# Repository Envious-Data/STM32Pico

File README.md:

# STM32Pico
A STM32 board in the format of a raspberry pi pico.

Im making this just so I can test out some other MCUs and also learn more about MCU board design, because I have things that use the raspberry pi pico I would like to make some replacements if there is a particular use case.

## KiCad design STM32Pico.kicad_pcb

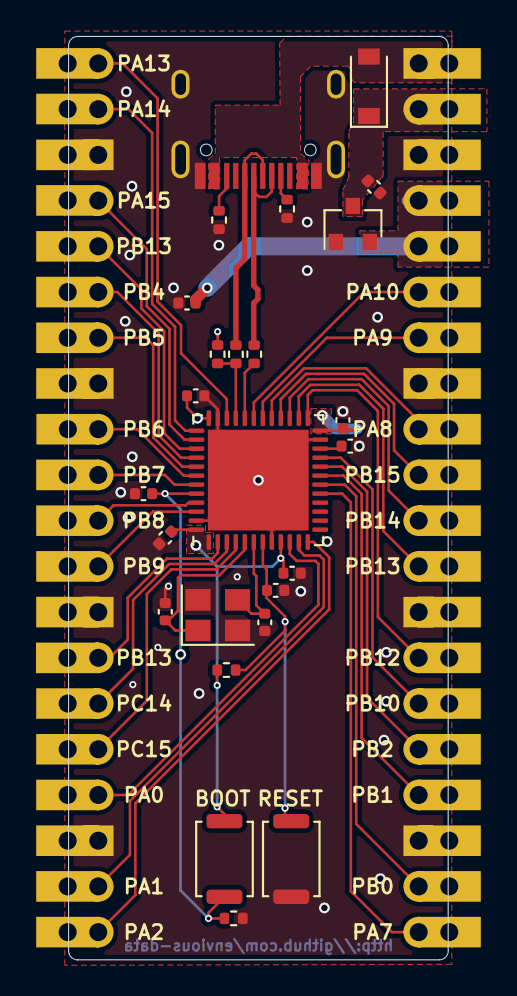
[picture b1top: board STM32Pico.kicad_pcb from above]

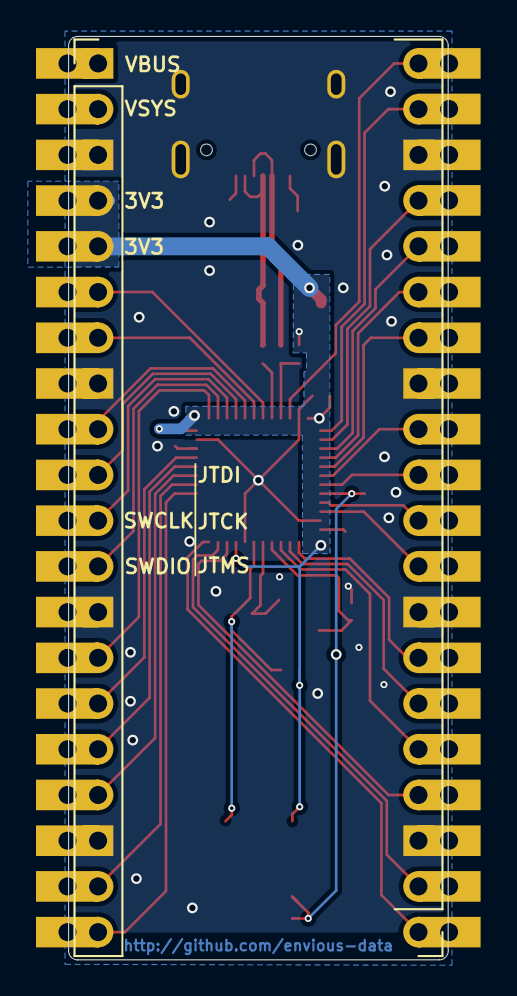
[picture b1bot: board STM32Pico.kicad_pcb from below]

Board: 2 copper layers, 21.1 x 51.3 mm, 27 parts (2 on the bottom side), 43 nets.

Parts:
C1: 2.2uF 0402; C_0402_1005Metric
C2, C3, C4, C5: 100nf capacitor; C_0402_1005Metric
C6, C7: 1uf capacitor; C_0402_1005Metric
C8, C9: 100nf 0402; C_0402_1005Metric
C10, C11: 22pf capacitor; C_0402_1005Metric
D1: 1N4002; D_SOD-123
J1, J2: 2.54mm header 01x20; PinHeader_1x20_P2.54mm_Vertical
R1, R2: 5.1K 0402; R_0402_1005Metric
R3, R4: 22ohm; R_0402_1005Metric
R5: 1.5K 0402; R_0402_1005Metric
R6: 10K 0402; R_0402_1005Metric
R7: 100k 0402; R_0402_1005Metric
SW1: Boot Mode; SW_Push_SPST_NO_Alps_SKRK
SW2: Reset Switch; SW_Push_SPST_NO_Alps_SKRK
U1: STM32F411CEUx; QFN-48-1EP_7x7mm_P0.5mm_EP5.6x5.6mm
U2: XC6206PxxxMR; SOT-23
USB1: HRO-TYPE-C-31-M-12; HRO-TYPE-C-31-M-12-Assembly
Y1: 8Mhz 3225; Crystal_SMD_3225-4Pin_3.2x2.5mm

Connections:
+3V3: C2.1, C3.2, C4.2, C5.2, C7.2, J2.4, J2.5, R5.1, R6.2, SW1.1, U1.1, U1.9, U1.24, U1.36, U1.48, U2.2
D+: R3.2, USB1.6, USB1.8
D-: R4.2, USB1.5, USB1.7
GND: C1.1, C2.2, C3.1, C4.1, C5.1, C6.1, C7.1, C8.2, C9.2, C10.2, C11.2, J1.3, J1.8, J1.13, J1.18, J2.3, J2.8, J2.13, J2.18, R1.1, R2.1, R7.2, SW2.1, U1.8, U1.23, U1.35, U1.47, U1.49, U2.1, USB1.1, USB1.12, USB1.13, Y1.2, Y1.4
unnamed: C1.2, U1.22
unnamed: R1.2, USB1.4
unnamed: R2.2, USB1.10
OSCIN: C10.1, U1.5, Y1.1
OSCOUT: C11.1, U1.6, Y1.3
PA0: J1.4, U1.10
PA1: J1.2, U1.11
PA2: J1.1, U1.12
PA7: J2.20, U1.17
PA8: J2.9, U1.29
PA9: J2.7, U1.30
PA10: J2.6, U1.31
PA11: R4.1, U1.32
PA12: R3.1, R5.2, U1.33
PA13-SWDIO: J1.20, U1.34
PA14-SWCLK: J1.19, U1.37
PA15: J1.17, U1.38
PB0: J2.19, U1.18
PB1: J2.17, U1.19
PB2: J2.16, U1.20
PB3: J1.16, U1.39
PB4: J1.15, U1.40
PB5: J1.14, U1.41
PB6: J1.12, U1.42
PB7: J1.11, U1.43
PB8: J1.10, U1.45
PB9: J1.9, U1.46
PB10: J2.15, U1.21
PB12: J2.14, U1.25
PB13: J2.12, U1.26
PB14: J2.11, U1.27
PB15: J2.10, U1.28
PC13: J1.7, U1.2
PC14: J1.6, U1.3
PC15: J1.5, U1.4
VBUS: D1.2, J2.1, USB1.2, USB1.11
VSYS: C6.2, D1.1, J2.2, U2.3
boot0: C8.1, R7.1, SW1.2, U1.44
resetsw: C9.1, R6.1, SW2.2, U1.7

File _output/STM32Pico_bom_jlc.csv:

"Comment","Designator","Footprint","LCSC Part #"
"2.2uF 0402","C1","C_0402_1005Metric","no_part_number"
"100nf capacitor","C2,C3,C4,C5","C_0402_1005Metric","no_part_number"
"1uf capacitor","C7,C6","C_0402_1005Metric","no_part_number"
"100nf 0402","C8,C9","C_0402_1005Metric","no_part_number"
"22pf capacitor","C10,C11","C_0402_1005Metric","no_part_number"
"1N4002","D1","D_SOD-123","no_part_number"
"2.54mm header 01x20","J2,J1","PinHeader_1x20_P2.54mm_Vertical","no_part_number"
"5.1K 0402","R1,R2","R_0402_1005Metric","no_part_number"
"22ohm","R3,R4","R_0402_1005Metric","no_part_number"
"1.5K 0402","R5","R_0402_1005Metric","no_part_number"
"10K 0402","R6","R_0402_1005Metric","no_part_number"
"100k 0402","R7","R_0402_1005Metric","no_part_number"
"Boot Mode","SW1","SW_Push_SPST_NO_Alps_SKRK","no_part_number"
"Reset Switch","SW2","SW_Push_SPST_NO_Alps_SKRK","no_part_number"
"STM32F411CEUx","U1","QFN-48-1EP_7x7mm_P0.5mm_EP5.6x5.6mm","no_part_number"
"XC6206PxxxMR","U2","SOT-23","no_part_number"
"HRO-TYPE-C-31-M-12","USB1","HRO-TYPE-C-31-M-12-Assembly","no_part_number"
"8Mhz 3225","Y1","Crystal_SMD_3225-4Pin_3.2x2.5mm","no_part_number"

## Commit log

2021-07-30 Added files
2021-07-30 worked on the PCB a bit more, added some zones. yet to assign pins to GPIOs
2021-07-30 finished up board design, likely needs some check overs and revision.
2021-07-30 cleaned up some bits and pieces.
2021-07-30 added image
2021-07-31 Generated some JLCPCB compatible Gerbers.
2021-08-14 properly seperated VBUS and VSYS however VSYS is now 5V output only since its not connected to the power management IC
2021-08-14 changed my mind - moved power ic to vsys and also adjusted USB traces to correct some phase skew.
2021-08-14 fixed the disconnected vsys pin and corrected all via sizes and placements
2021-09-18 added pin lables and Jtag/swdio/swclk on the PCB
2021-09-18 changed diode for more common type
2021-09-18 Generated Updated Gerbers
2021-09-18 adjusted pin labels
2021-09-18 updated gerber
2021-11-16 swapped oscilator for crystal and adjusted various nearby parts and traces.
2021-11-16 generated updated gerber
2021-11-17 added github url and fixed usb traces to not require vias
2021-11-20 fixed some stuff and generated updated gerber
2021-11-29 moved couple vias off pads
